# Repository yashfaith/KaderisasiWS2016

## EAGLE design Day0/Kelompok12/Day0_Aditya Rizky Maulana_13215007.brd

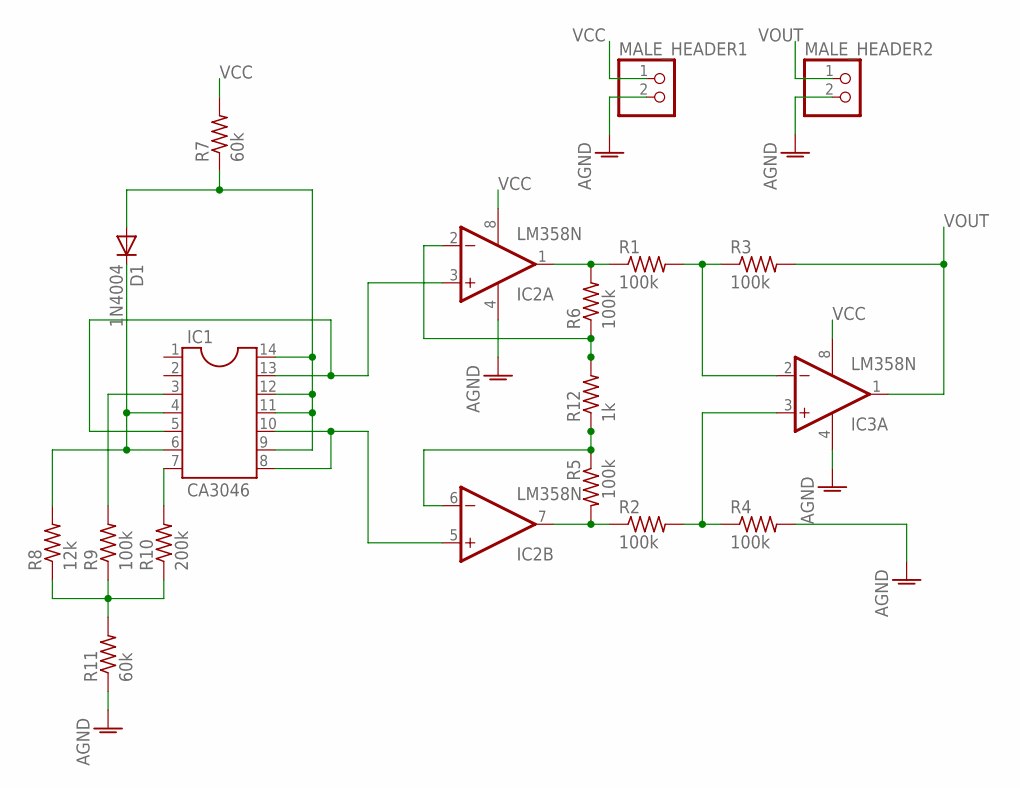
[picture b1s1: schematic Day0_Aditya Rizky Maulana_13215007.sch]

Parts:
D1: 1N4004; DO41-10
IC1: CA3046; DIL14
IC2, IC3: LM358N; DIL08
MALE_HEADER1, MALE_HEADER2: PINHD-1X2; 1X02
R1, R2, R3, R4, R5, R6, R9: 100k; 0207/7
R7, R11: 60k; 0207/7
R8: 12k; 0207/7
R10: 200k; 0207/7
R12: 1k; 0207/7

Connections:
AGND: IC2.4 (V-), IC3.4 (V-), MALE_HEADER1.2, MALE_HEADER2.2, R4.2, R11.1
unnamed: IC2.2 (-IN), R6.1, R12.2
unnamed: IC1.8, IC1.10, IC2.5 (+IN)
unnamed: IC2.7 (OUT), R2.1, R5.2
unnamed: IC2.1 (OUT), R1.1, R6.2
unnamed: IC1.5, IC1.13, IC2.3 (+IN)
unnamed: IC2.6 (-IN), R5.1, R12.1
unnamed: IC3.2 (-IN), R1.2, R3.1
unnamed: IC3.3 (+IN), R2.2, R4.1
unnamed: IC1.7, R10.2
unnamed: D1.C, IC1.4, IC1.6, R8.2
unnamed: IC1.3, R9.2
unnamed: D1.A, IC1.9, IC1.11, IC1.12, IC1.14, R7.1
unnamed: R8.1, R9.1, R10.1, R11.2
VCC: IC2.8 (V+), IC3.8 (V+), MALE_HEADER1.1, R7.2
VOUT: IC3.1 (OUT), MALE_HEADER2.1, R3.2

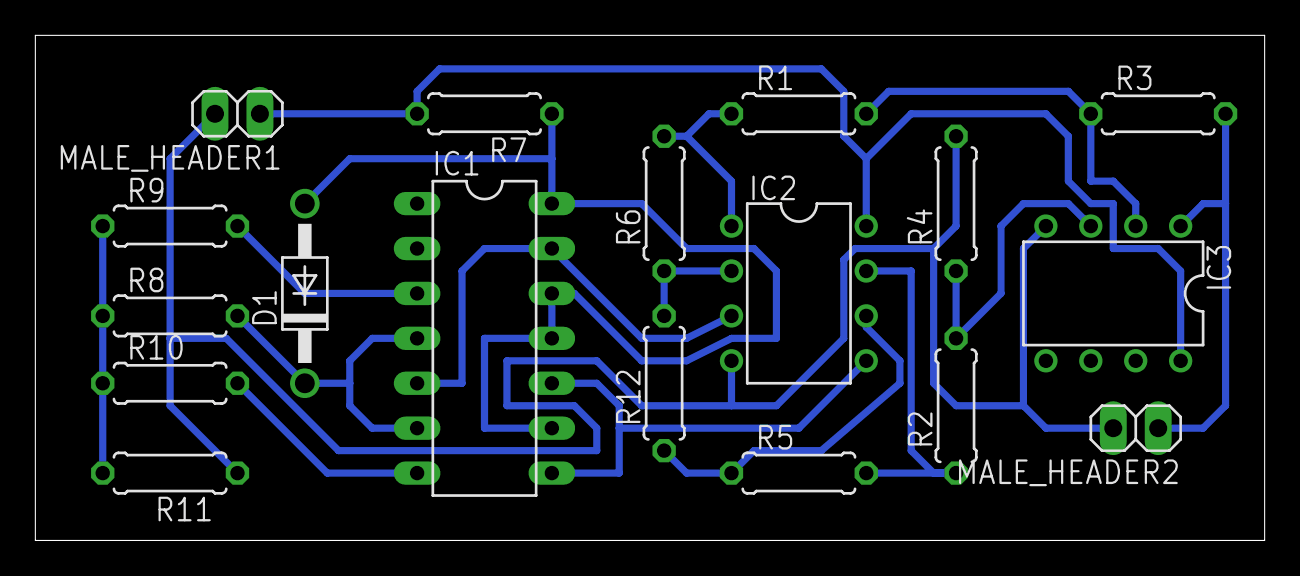
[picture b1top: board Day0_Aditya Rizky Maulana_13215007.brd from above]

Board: 2 copper layers, 69.5 x 28.6 mm, 18 parts (0 on the bottom side), 16 nets.

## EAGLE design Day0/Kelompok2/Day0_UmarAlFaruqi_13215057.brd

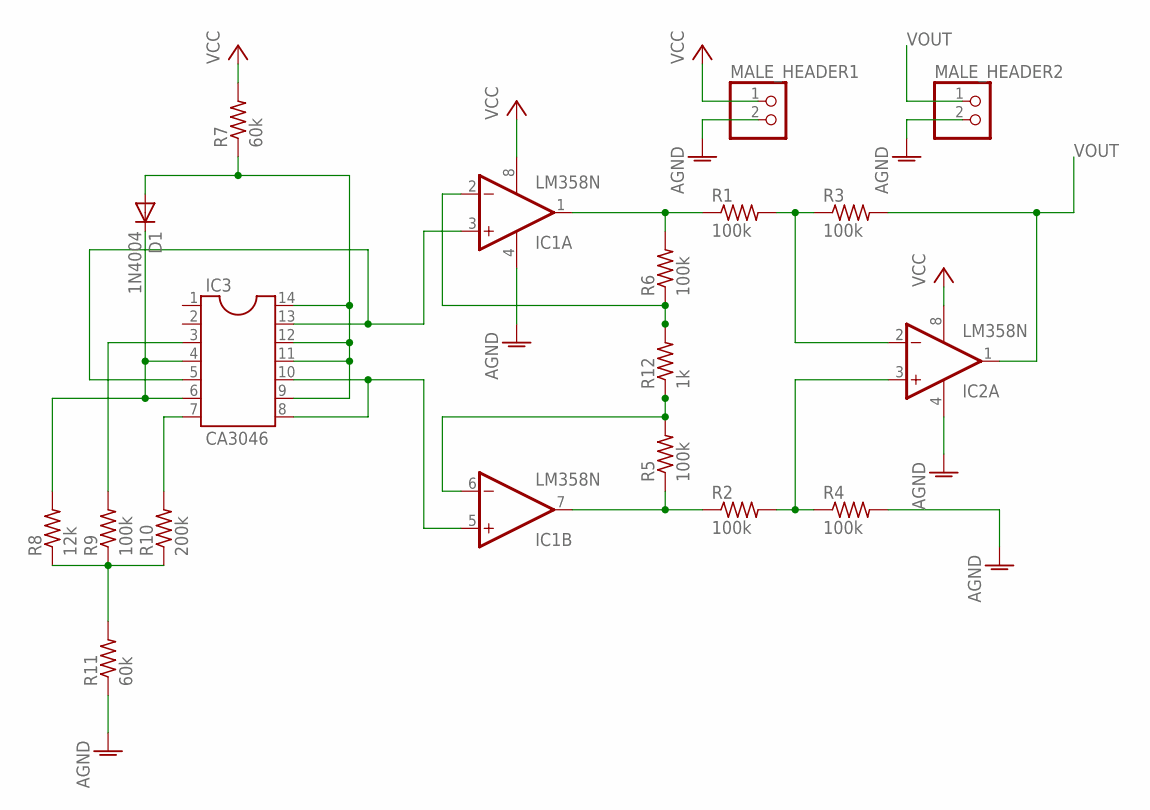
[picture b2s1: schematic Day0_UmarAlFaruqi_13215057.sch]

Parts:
D1: 1N4004; DO41-10
IC1, IC2: LM358N; DIL08
IC3: CA3046; DIL14
MALE_HEADER1, MALE_HEADER2: PINHD-1X2; 1X02
R1, R2, R3, R4, R5, R6, R9: 100k; 0204V
R7, R11: 60k; 0204V
R8: 12k; 0204V
R10: 200k; 0204V
R12: 1k; 0204V

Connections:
AGND: IC1.4 (V-), IC2.4 (V-), MALE_HEADER1.2, MALE_HEADER2.2, R4.2, R11.1
unnamed: D1.A, IC3.9, IC3.11, IC3.12, IC3.14, R7.1
unnamed: D1.C, IC3.4, IC3.6, R8.2
unnamed: IC3.7, R10.2
unnamed: IC3.3, R9.2
unnamed: IC1.3 (+IN), IC3.5, IC3.13
unnamed: IC1.5 (+IN), IC3.8, IC3.10
unnamed: R8.1, R9.1, R10.1, R11.2
unnamed: IC1.2 (-IN), R6.1, R12.2
unnamed: IC1.1 (OUT), R1.1, R6.2
unnamed: IC2.2 (-IN), R1.2, R3.1
unnamed: IC1.6 (-IN), R5.2, R12.1
unnamed: IC1.7 (OUT), R2.1, R5.1
unnamed: IC2.3 (+IN), R2.2, R4.1
VCC: IC1.8 (V+), IC2.8 (V+), MALE_HEADER1.1, R7.2
VOUT: IC2.1 (OUT), MALE_HEADER2.1, R3.2

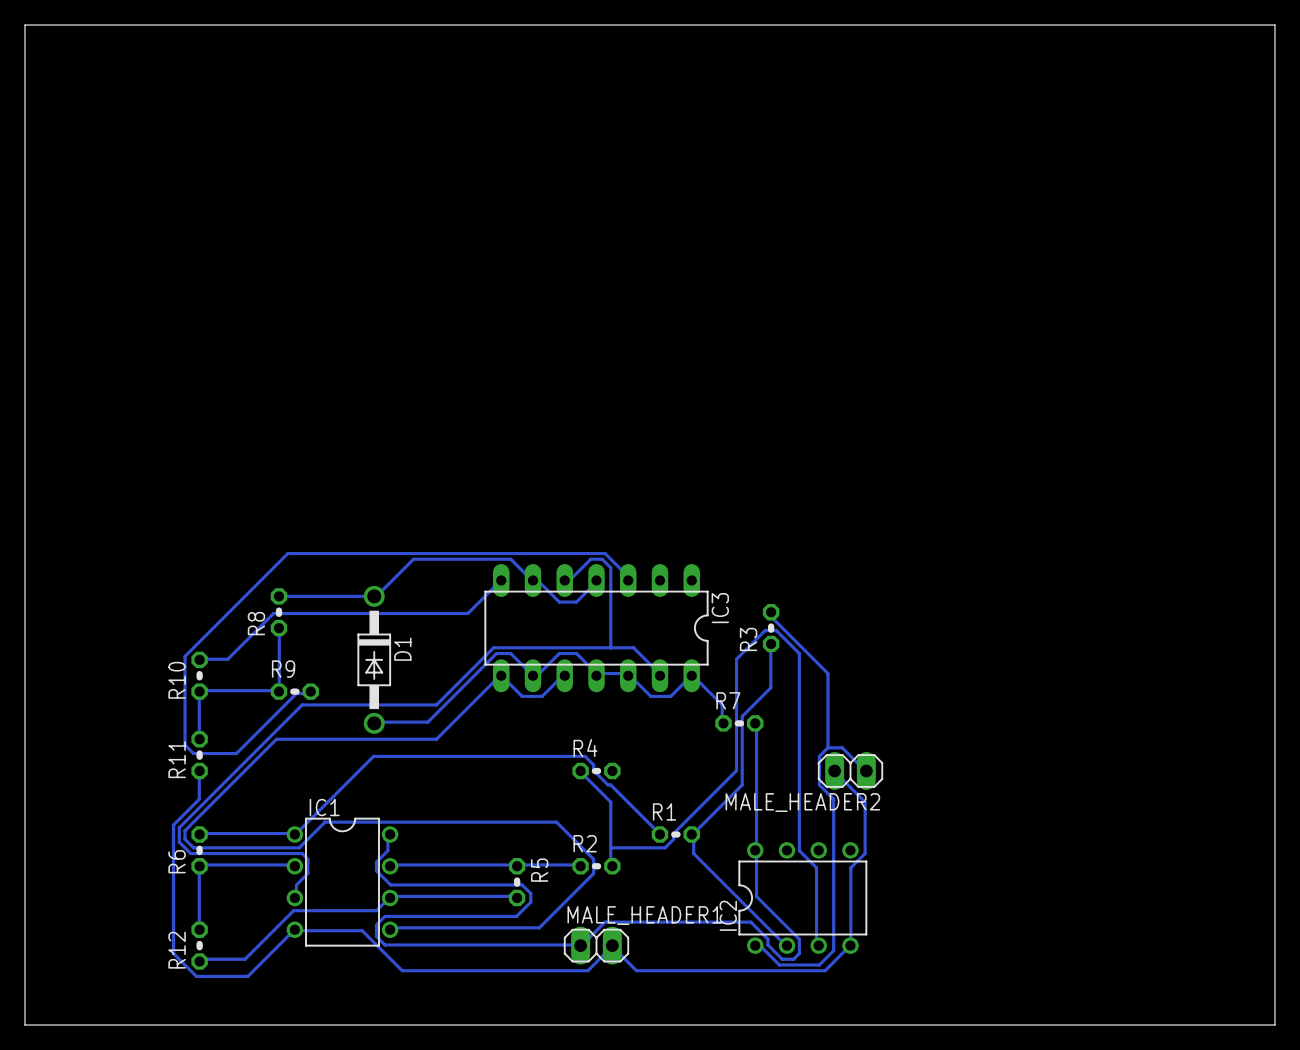
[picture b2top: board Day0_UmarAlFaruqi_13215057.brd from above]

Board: 2 copper layers, 100.0 x 80.0 mm, 18 parts (0 on the bottom side), 16 nets.

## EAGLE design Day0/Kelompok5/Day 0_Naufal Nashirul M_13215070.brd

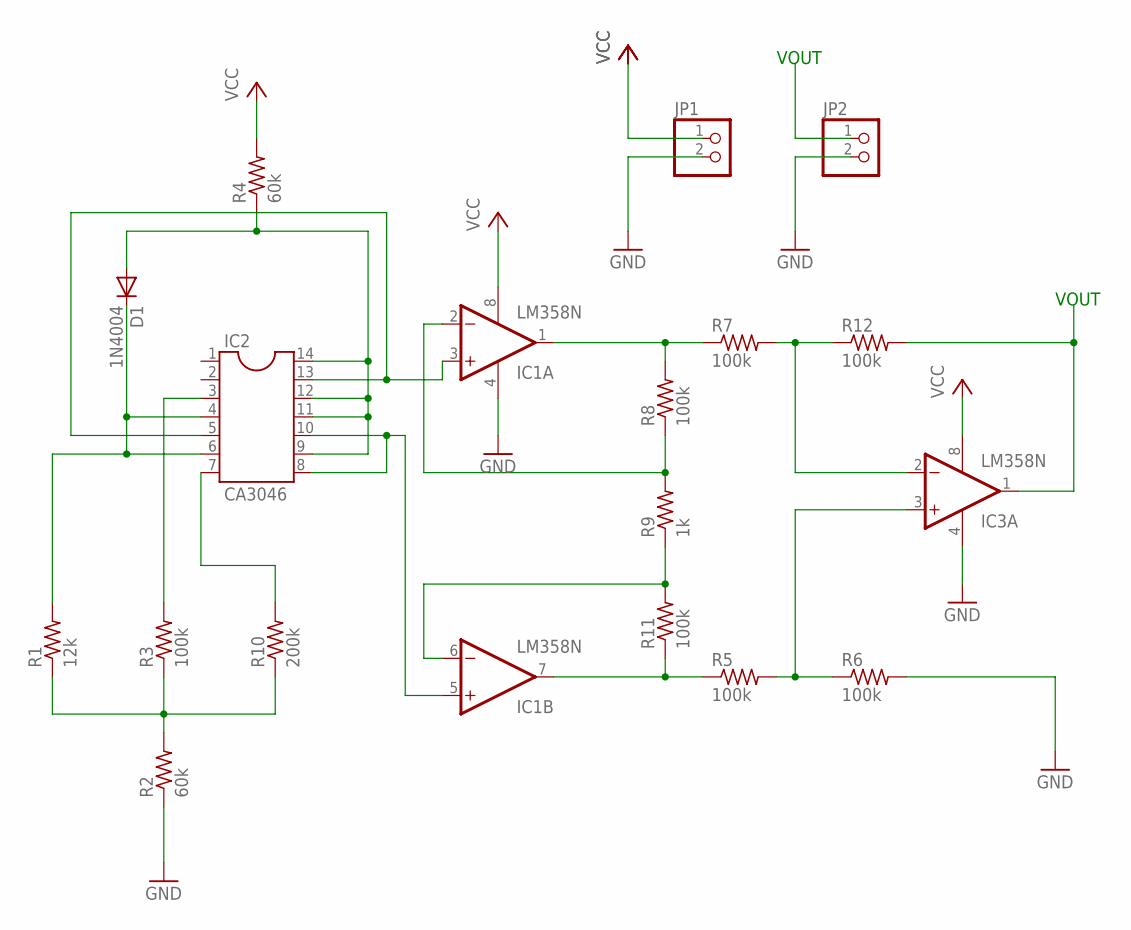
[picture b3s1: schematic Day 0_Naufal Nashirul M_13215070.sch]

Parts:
D1: 1N4004; D-7.5
IC1, IC3: LM358N; DIL08
IC2: CA3046; DIL14
JP1, JP2: PINHD-1X2; 1X02
R1: 12k; 0204/7
R2, R4: 60k; 0204/7
R3, R5, R6, R7, R8, R11, R12: 100k; 0204/7
R9: 1k; 0204/7
R10: 200k; 0204/7

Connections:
GND: IC1.4 (V-), IC3.4 (V-), JP1.2, JP2.2, R2.1, R6.2
MALE_HEADER1: JP1.1
unnamed: D1.A, IC2.9, IC2.11, IC2.12, IC2.14, R4.1
unnamed: D1.C, IC2.4, IC2.6, R1.2
unnamed: IC2.3, R3.2
unnamed: IC2.7, R10.2
unnamed: R1.1, R2.2, R3.1, R10.1
unnamed: IC1.1 (OUT), R7.1, R8.2
unnamed: IC1.3 (+IN), IC2.5, IC2.13
unnamed: IC1.5 (+IN), IC2.8, IC2.10
unnamed: IC3.2 (-IN), R7.2, R12.1
unnamed: IC1.2 (-IN), R8.1, R9.2
unnamed: IC1.7 (OUT), R5.1, R11.1
unnamed: IC3.3 (+IN), R5.2, R6.1
unnamed: IC1.6 (-IN), R9.1, R11.2
unnamed: IC3.1 (OUT), R12.2
VCC: IC1.8 (V+), IC3.8 (V+), R4.2

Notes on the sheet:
VOUT

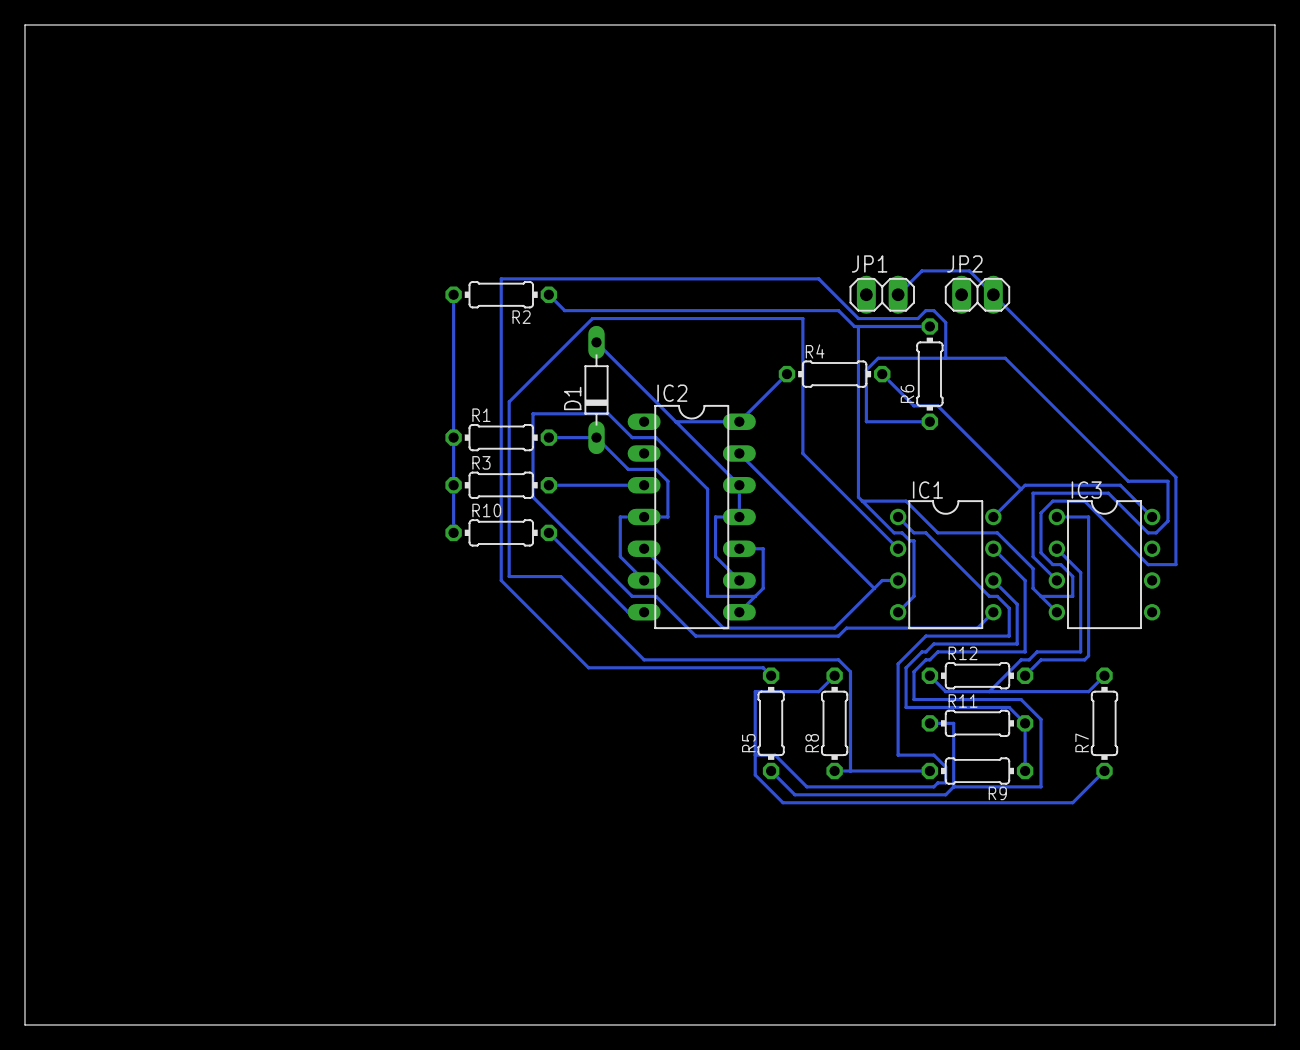
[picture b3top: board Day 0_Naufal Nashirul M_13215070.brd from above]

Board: 2 copper layers, 100.0 x 80.0 mm, 18 parts (0 on the bottom side), 16 nets.

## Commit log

2016-09-22 Kelompok2/
2016-09-22 Tugas Day 0 Kelompok 2
2016-09-22 Revert "Tugas Day 0 Kelompok 4"
2016-09-23 Create Kelompok11
